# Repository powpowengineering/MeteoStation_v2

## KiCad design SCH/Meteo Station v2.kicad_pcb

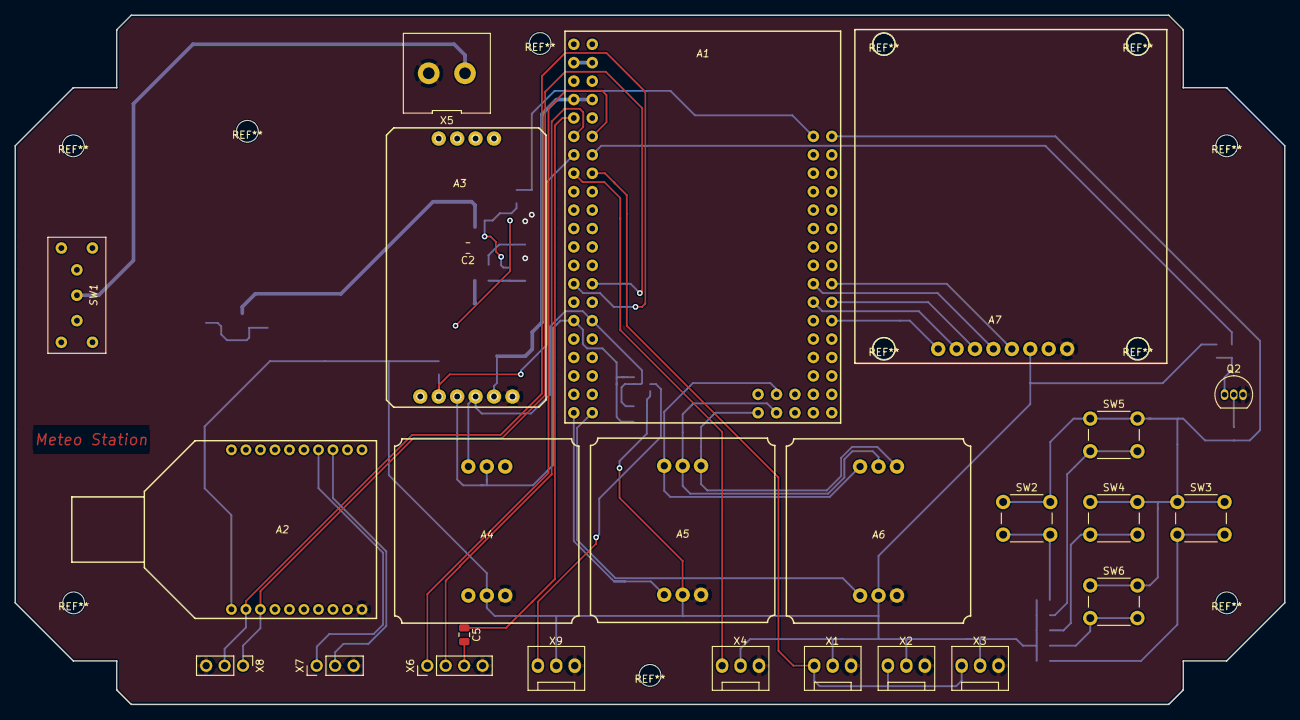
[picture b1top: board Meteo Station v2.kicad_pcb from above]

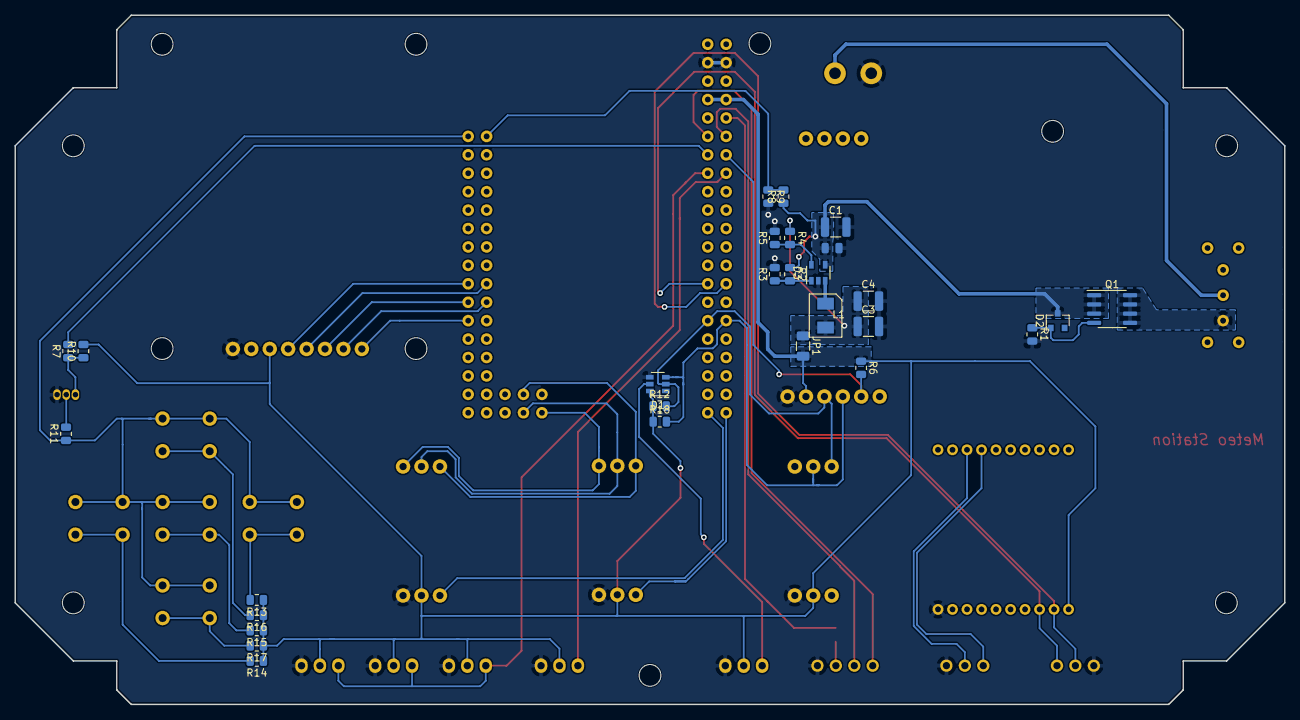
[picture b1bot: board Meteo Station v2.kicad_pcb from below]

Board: 2 copper layers, 175.0 x 95.0 mm, 52 parts (27 on the bottom side), 44 nets.

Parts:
A1: ArduinoMega2560; arduinoMega2560
A2: WisDuo_RAK811; RAK811_WisDuo
A3: Module_RTC_DS3231
A4: Module_LPS25HB; Module_Troyka
A5, A6: Module_SD_CARD; Module_Troyka
A7: Module_Lcd_5110; Module_LCD5110
C1, C3, C4: 10uf; C_1210_3225Metric
C2: 0,1uf; C_0805_2012Metric
C5: 100 nf; C_0805_2012Metric
D1: DS2484; SOT-23-6
D2: BZX84Cxx; D_SOT-23_ANK
D3: TPS560200; SOT-23-5
JP1: Jumper_2_Bridged; Fuse_1206_3216Metric
L1: 10uH; L_TDK_SMP4020
Q1: IRF7410; SOIC-8_3.9x4.9mm_P1.27mm
Q2: BC337; TO-92_Inline
R1, R2, R3, R12, R18: R; R_0805_2012Metric
R4: 62k 1%; R_0805_2012Metric
R5: 20k 1%; R_0805_2012Metric
R6, R7, R8, R9, R10, R11, R13, R14, R15, R16, R17: 4,7K; R_0805_2012Metric
SW1: SW_DPDT; SIP-3
SW2, SW3, SW4, SW5, SW6: SW_MEC_5E; SW_PUSH_6mm
X1: TempSensor_1; FanPinHeader_1x03_P2.54mm_Vertical
X2: TempSensor_2; FanPinHeader_1x03_P2.54mm_Vertical
X3: TempSensor_3; FanPinHeader_1x03_P2.54mm_Vertical
X4: HumiditySensor; FanPinHeader_1x03_P2.54mm_Vertical
X5: Screw_Terminal_01x02; KLS2-128I-5
X6: COM_PORT; PinHeader_1x04_P2.54mm_Vertical
X7, X8: COM_PORT; PinHeader_1x03_P2.54mm_Vertical
X9: PressureSensor; FanPinHeader_1x03_P2.54mm_Vertical

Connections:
+3V3: A1.7, A1.8, A2.1, A3.5, A4.5, A5.5, A6.5, A7.6, D1.6, JP1.2, R6.1, R10.2, R12.1, R13.1, R14.1, R15.1, R16.1, R17.1, R18.1, X1.2, X2.2, X3.2, X4.2, X9.2
+BATT: C1.1, C2.1, D2.1, D3.4, Q1.1, Q1.2, Q1.3, R2.1, R8.1
/BUTTONS: A1.A0, R11.1, SW2.1, SW2.2, SW3.1, SW3.2, SW4.1, SW4.2, SW5.1, SW5.2, SW6.1, SW6.2
/CS_SD_1: A1.D31, A5.6
/CS_SD_2: A1.D30, A6.6
/D32: A1.D32, A7.5
/D33: A1.D33, A7.4
/D34: A1.D34, A7.3
/D35: A1.D35, A7.2
/D36: A1.D36, A7.1
/DATA_BMP280: D1.5, X9.1
/DATA_HUM: A1.D5, X4.1
/DATA_TEMP: A1.D4, X1.1, X2.1, X3.1
/INT4_BUTTON: A1.D2, R7.2
/INT5_RTC: A1.D3, A3.2, R6.2
/MISO: A1.D50, A5.2, A6.2
/MOSI: A1.D51, A5.1, A6.1
/RXD: A1.D0, X6.1
/RX_LORA: A1.D16, A2.3, X8.1
/SCL: A1.D21, A3.3, A4.2, D1.3, R18.2
/SDA: A1.D20, A3.4, A4.1, D1.2, R12.2
/SPI_SCK: A1.D52, A5.3, A6.3
/SWCLK: A2.13, X7.2
/SWDIO: A2.14, X7.1
/TXD: A1.D1, X6.2
/TX_LORA: A1.D17, A2.2, X8.2
/VBAT_MEAS: A1.A1, R8.2, R9.1
/~RST: A1.9, C5.1
GND: A1.3, A1.4, A2.10, A3.6, A4.4, A5.4, A6.4, A7.8, C1.2, C2.2, C3.2, C4.2, D1.4, D3.2, Q2.3, R1.2, R3.2, R5.2, R9.2, X1.3, X2.3, X3.3, X4.3, X5.2, X6.4, X7.3, X8.3, X9.3
unnamed: C3.1, C4.1, JP1.1, L1.2, R4.1
unnamed: C5.2, X6.3
unnamed: D2.2, Q1.4, R1.1
unnamed: D3.1, R2.2, R3.1
unnamed: D3.3, L1.1
unnamed: D3.5, R4.2, R5.1
unnamed: Q1.5, Q1.6, Q1.7, Q1.8, SW1.1
unnamed: Q2.1, R7.1, R10.1
unnamed: Q2.2, R11.2
unnamed: R13.2, SW2.3, SW2.4
unnamed: R14.2, SW3.3, SW3.4
unnamed: R15.2, SW4.3, SW4.4
unnamed: R16.2, SW5.3, SW5.4
unnamed: R17.2, SW6.3, SW6.4
unnamed: SW1.2, X5.1

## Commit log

2022-03-29 Added CMake files
2022-04-12 Added project
2022-04-13 Changed absolute path to local path
2022-04-15 Added template files
2022-04-15 Added fun init
2022-04-16 Added functions: init,reset,readBit,writeBit,readByte,writeByte,Gpioinit,DQLow,DQInput,DQGetValue
2022-04-16 Added OneWire in make
2022-04-16 Added config TIM6 and function INIT_Delay()
2022-04-16 Added calls function
2022-04-16 Added files init_cfg.h and Init.h
2022-04-17 Added function DS18B20_GetID, DS18B20_GetTemperature
2022-04-23 Added fun write scratchpad
2022-04-26 Added SetResolution
2022-05-01 Added channel number in parameters
2022-05-01 Added USART driver files
2022-05-02 Added USART_Init USART_PutCharacter
2022-05-06 Changed config USART driver pins
2022-05-07 Added AM2305_Init()
2022-05-08 Added function AM2305_GetHumidityTemperature()
2022-05-08 Added files W25Q_drv.c W25Q_drv_cfg.h W25Q_drv.h ; Added W25Q_Init() function
2022-05-09 Added W25Q_ReadWriteSPI,W25Q_ReadData
2022-05-14 Added Erase function
2022-05-15 Finished AM2305_GetHumidityTemperature
2022-05-15 Added BME280 driver
2022-05-15 Fixed GetHumidityTemperature function
2022-05-20 Added read ID
2022-05-20 Added task flash test
2022-05-20 Added test function
2022-05-28 Added W25Q_TIMES strc, fixed some bugs
2022-05-28 Added crc module
2022-05-28 Added new paths
2022-05-28 Added test flash
2022-05-28 added lidar code
2022-05-28 Added Test 1
2022-05-28 Added critical section
2022-05-28 Added result
2022-05-28 Fixed bug Erase Chip command
2022-05-28 Added Test 1, Test 2
2022-05-28 Changed settings
2022-05-29 Added diagram
2022-05-29 Added SCH
2022-05-29 Added local settings
2022-05-29 added anemometer
2022-05-29 added software start ADC1
2022-05-29 Fixed bug calculate adr
2022-06-04 Added GetLock
2022-06-04 Added test 1 test 2
2022-06-11 Added task_mqtt
2022-06-12 Added test e-paper
2022-06-12 Added init bme280
2022-06-12 Added generate bin file
2022-06-12 Fixid the syntax
2022-07-01 Send mqtt without lib
2022-07-03 Added Lidar driver LF02pro
2022-07-03 Added coreMQTT driver
2022-07-03 Added Reading lidar data
2022-07-03 Removed BME280 driver
2022-07-03 Added bmp2 driver
2022-07-03 Added additional settings
2022-07-08 Added CMSIS_RTOS_V2
2022-07-08 Added lwgsm
2022-07-10 Added comunication with rightech , send tem,humidity,pressure
2022-07-11 Fixed bug - clear data[] before read data from senser
2022-07-14 Added critical zone before set mod bmp280
2022-07-17 Corrected puth
2022-07-17 added eeprom emulation lib
2022-07-19 Added path of EEPROM Emulation
2022-07-19 Added task_test_EE files
2022-07-19 Removed TF02_PRO build
2022-07-19 Added lib in project and adapted for stm32L151
2022-07-19 Added test writing data in EE
2022-07-20 added flash erase sector function
2022-07-21 added test EE with wwriting in W24Q
2022-07-21 Added CmakeScripts dir
2022-07-21 Removed files
2022-07-25 Adapted W25Q driver for HAL
2022-07-26 Adapted code for HAL
2022-07-28 Added test write records to flash and eeprom
2022-08-02 Added test write flash and eeprom emulation
2022-08-04 Fixed bug in createRecord fun
2022-08-04 Added task_mqtt_cfg file
2022-08-04 Added mqtt
2022-08-04 Added task_master files
2022-08-04 Added record manager driver
2022-08-04 Added diagrams
2022-08-05 Added interface function in record manager
2022-08-08 Added Store, Store, CreateRecord,ParsingRecord
2022-08-09 Fixed CreateRecord function and Parsing Function
2022-08-09 Added ReadVariable32 WriteVariable32 functions
2022-08-09 Added CalculateCRC8WithBegin function
2022-08-09 Added config for uart terminal
2022-08-09 Added path record manager
2022-08-09 Corrected tasks to new diagram
2022-08-09 Added terminal
2022-08-09 Stop tracking toolchan file
2022-08-09 Added tasj master path
2022-08-09 Added neww command
2022-08-09 Removed definition virtual addresses
2022-08-09 Added definition virtual addresses
2022-08-10 Added fix size record
2022-08-10 Corrected Load function
2022-08-11 Added writing in wlash by yask_read_sens
2022-08-11 Added task_GSM files
2022-08-12 Added type of record
2022-08-12 Added setting UART for GSM module
2022-08-15 Added I2C HAL
2022-08-15 Added puth I2C
2022-08-15 Updated user_i2c_read to use HAL
2022-08-15 Ported oneWire driver to HAL
2022-08-16 Ported half of am2305 driver to HAL
2022-08-17 Updated am2305 driver for HAL
2022-08-18 Added control pin
2022-08-21 Added measure battery voltage and anemometer
2022-08-24 Added RTC step1
2022-08-25 Added RTC step2
2022-08-26 Added RTC and standby step3
2022-08-28 Added send to thingspeak server
2022-08-29 Added test with send message to thingspeak server
2022-08-30 Fixed begin value eeprom array
2022-08-30 Added alarm B
2022-08-31 Added eeprom emulation v.2
2022-09-01 Added eeprom_emulation v.2 step2
2022-09-01 Added eeprom emilation v.2 step 3
2022-09-02 Added task terminal, fixed W25q driver
2022-09-02 Added time driver
2022-09-03 Added SetTime function and SetDate function
2022-09-04 Added control GSM DC/DC
2022-09-06 Fixed ADC configuration bug
2022-09-07 Set alarm 1 hour
2022-09-07 Added setalarm sens step1
2022-09-26 Added circular buffer
2022-09-26 Corrected Time driver
2022-09-26 Updated CmakeList
2022-11-04 Updated task_master
2023-11-05 Add read temperature draft
